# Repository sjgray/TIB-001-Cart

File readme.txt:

This is a project to clone the TIB-001 Drive for the C64.
The TIB drive uses a standard Floppy Disk Controller (FDC)
along with custom Firmware and a standard 3.5" floppy mechanism.

Once cloned my goal is to adapt this to other Commodore systems.

Schematics are drawn with Kicad.

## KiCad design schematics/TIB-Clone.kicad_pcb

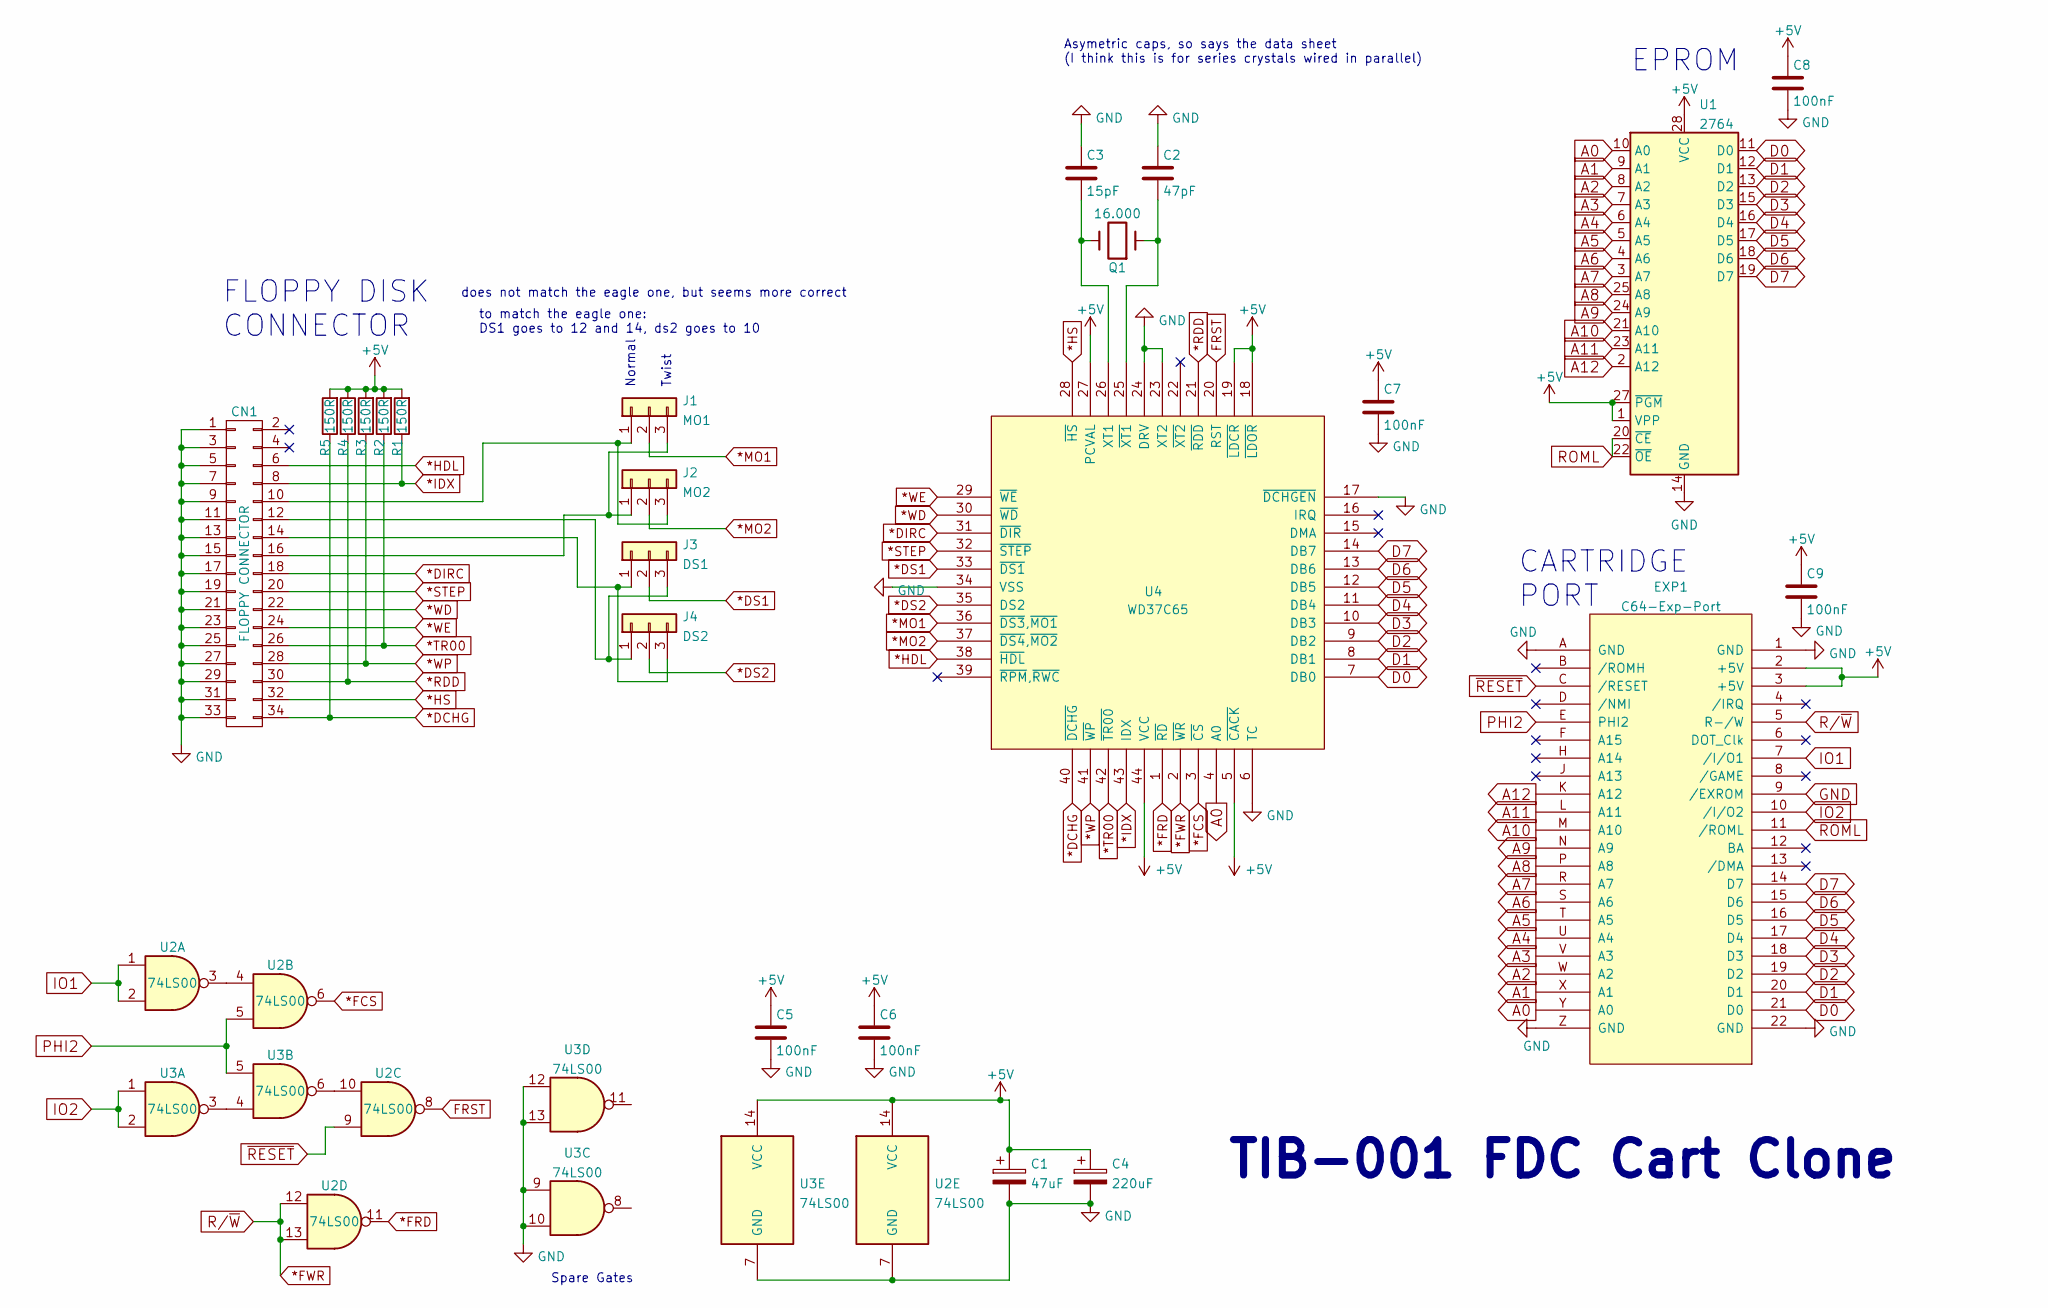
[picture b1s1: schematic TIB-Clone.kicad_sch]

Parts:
C1: 47uF; CP_Radial_D5.0mm_P2.50mm
C2: 47pF; C_Disc_D4.7mm_W2.5mm_P5.00mm
C3: 15pF; C_Disc_D4.7mm_W2.5mm_P5.00mm
C4: 220uF; CP_Radial_D6.3mm_P2.50mm
C5, C6, C7, C8, C9: 100nF; C_Disc_D4.7mm_W2.5mm_P5.00mm
CN1: FLOPPY CONNECTOR; PinHeader_2x17_P2.54mm_Vertical
EXP1: C64-Exp-Port; C64-Cart-NoSilkS
J1: MO1; SolderJumper-3_P2.0mm_Open_TrianglePad1.0x1.5mm_NumberLabels
J2: MO2; SolderJumper-3_P2.0mm_Open_TrianglePad1.0x1.5mm_NumberLabels
J3: DS1; SolderJumper-3_P2.0mm_Open_TrianglePad1.0x1.5mm_NumberLabels
J4: DS2; SolderJumper-3_P2.0mm_Open_TrianglePad1.0x1.5mm_NumberLabels
Q1: 16.000; Crystal_HC49-U_Vertical
R1, R2, R3, R4, R5: 150R; R_Axial_DIN0207_L6.3mm_D2.5mm_P10.16mm_Horizontal
U1: 2764; DIP-28_W15.24mm
U2, U3: 74LS00; DIP-14_W7.62mm
U4: WD37C65; PLCC-44

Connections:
*DCHG: CN1.34, R5.1, U4.40 (~DCHG)
*DIRC: CN1.18, U4.31 (~DIR)
*DS1: J3.2, U4.33 (~DS1)
*DS2: J4.2, U4.35 (DS2)
*FCS: U2.6, U4.3 (~CS)
*FRD: U2.11, U4.1 (~RD)
*FWR: EXP1.5 (R-/W), U2.12, U2.13, U4.2 (~WR)
*HDL: CN1.6, U4.38 (~HDL)
*HS: CN1.32, U4.28 (~HS)
*IDX: CN1.8, R1.1, U4.43 (IDX)
*MO1: J1.2, U4.36 (~DS3,~MO1)
*MO2: J2.2, U4.37 (~DS4,~MO2)
*RDD: CN1.30, R4.2, U4.21 (~RDD)
*STEP: CN1.20, U4.32 (~STEP)
*TR00: CN1.26, R2.1, U4.42 (~TR00)
*WD: CN1.22, U4.30 (~WD)
*WE: CN1.24, U4.29 (~WE)
*WP: CN1.28, R3.1, U4.41 (~WP)
+5V: C1.1, C4.1, C5.1, C6.1, C7.1, C8.1, C9.1, EXP1.2 (+5V), EXP1.3 (+5V), R1.2, R2.2, R3.2, R4.1, R5.2, U1.1 (VPP), U1.27 (~PGM), U1.28 (VCC), U2.14 (VCC), U3.14 (VCC), U4.5 (~CACK), U4.18 (~LDOR), U4.19 (~LDCR), U4.27 (PCVAL), U4.44 (VCC)
A0: EXP1.Y (A0), U1.10 (A0), U4.4 (A0)
A1: EXP1.X (A1), U1.9 (A1)
A2: EXP1.W (A2), U1.8 (A2)
A3: EXP1.V (A3), U1.7 (A3)
A4: EXP1.U (A4), U1.6 (A4)
A5: EXP1.T (A5), U1.5 (A5)
A6: EXP1.S (A6), U1.4 (A6)
A7: EXP1.R (A7), U1.3 (A7)
A8: EXP1.P (A8), U1.25 (A8)
A9: EXP1.N (A9), U1.24 (A9)
A10: EXP1.M (A10), U1.21 (A10)
A11: EXP1.L (A11), U1.23 (A11)
A12: EXP1.K (A12), U1.2 (A12)
D0: EXP1.21 (D0), U1.11 (D0), U4.7 (DB0)
D1: EXP1.20 (D1), U1.12 (D1), U4.8 (DB1)
D2: EXP1.19 (D2), U1.13 (D2), U4.9 (DB2)
D3: EXP1.18 (D3), U1.15 (D3), U4.10 (DB3)
D4: EXP1.17 (D4), U1.16 (D4), U4.11 (DB4)
D5: EXP1.16 (D5), U1.17 (D5), U4.12 (DB5)
D6: EXP1.15 (D6), U1.18 (D6), U4.13 (DB6)
D7: EXP1.14 (D7), U1.19 (D7), U4.14 (DB7)
FRST: U2.8, U4.20 (RST)
GND: C1.2, C2.1, C3.1, C4.2, C5.2, C6.2, C7.2, C8.2, C9.2, CN1.1, CN1.3, CN1.5, CN1.7, CN1.9, CN1.11, CN1.13, CN1.15, CN1.17, CN1.19, CN1.21, CN1.23, CN1.25, CN1.27, CN1.29, CN1.31, CN1.33, EXP1.1 (GND), EXP1.9 (/EXROM), EXP1.22 (GND), EXP1.A (GND), EXP1.Z (GND), U1.14 (GND), U2.7 (GND), U3.7 (GND), U3.9, U3.10, U3.12, U3.13, U4.6 (TC), U4.17 (~DCHGEN), U4.23 (XT2), U4.24 (DRV), U4.34 (VSS)
IO1: EXP1.7 (/I/O1), U2.1, U2.2
IO2: EXP1.10 (/I/O2), U3.1, U3.2
unnamed: C2.2, Q1.1, U4.25 (~XT1)
unnamed: C3.2, Q1.2, U4.26 (XT1)
unnamed: CN1.10, J1.1, J2.3
unnamed: CN1.12, J3.3, J4.1
unnamed: CN1.14, J3.1, J4.3
unnamed: CN1.16, J1.3, J2.1
unnamed: U2.3, U2.4
unnamed: U3.3, U3.4
unnamed: U2.10, U3.6
PHI2: EXP1.E (PHI2), U2.5, U3.5
ROML: EXP1.11 (/ROML), U1.20 (~CE), U1.22 (~OE)
~RESET: EXP1.C (/RESET), U2.9

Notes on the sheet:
CARTRIDGE PORT
to match the eagle one: DS1 goes to 12 and 14, ds2 goes to 10
EPROM
Asymetric caps, so says the data sheet (I think this is for series crystals wired in parallel)
Twist
FLOPPY DISK CONNECTOR
TIB-001 FDC Cart Clone
Normal
Spare Gates
does not match the eagle one, but seems more correct

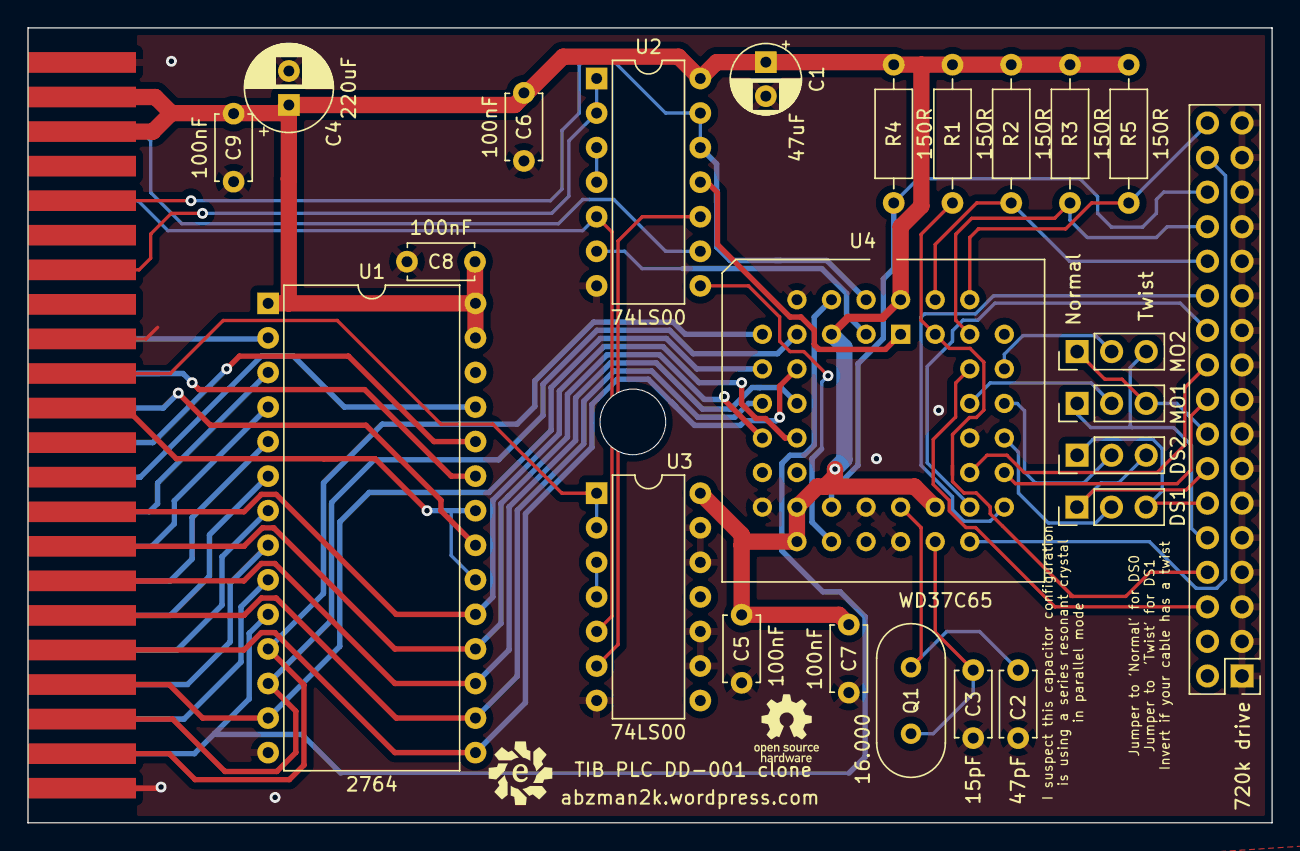
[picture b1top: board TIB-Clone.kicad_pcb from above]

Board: 2 copper layers, 91.4 x 58.4 mm, 25 parts (0 on the bottom side), 56 nets.

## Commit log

2018-04-15 :space_invader: Added .gitattributes & .gitignore files
2018-04-15 Initial upload
    This is the initial upload of pictures, firmware, and schematics.
2022-02-17 schematic and PCB completed
    kept the original rom as opposed to the big flash rom that the other clone did. I added the ability to swap between drive 0 and drive 1 rather than hardwiring it different than the original
2022-02-19 changed to through hole socket and through hole jumpers, fixed typo and added optional mounting hole
